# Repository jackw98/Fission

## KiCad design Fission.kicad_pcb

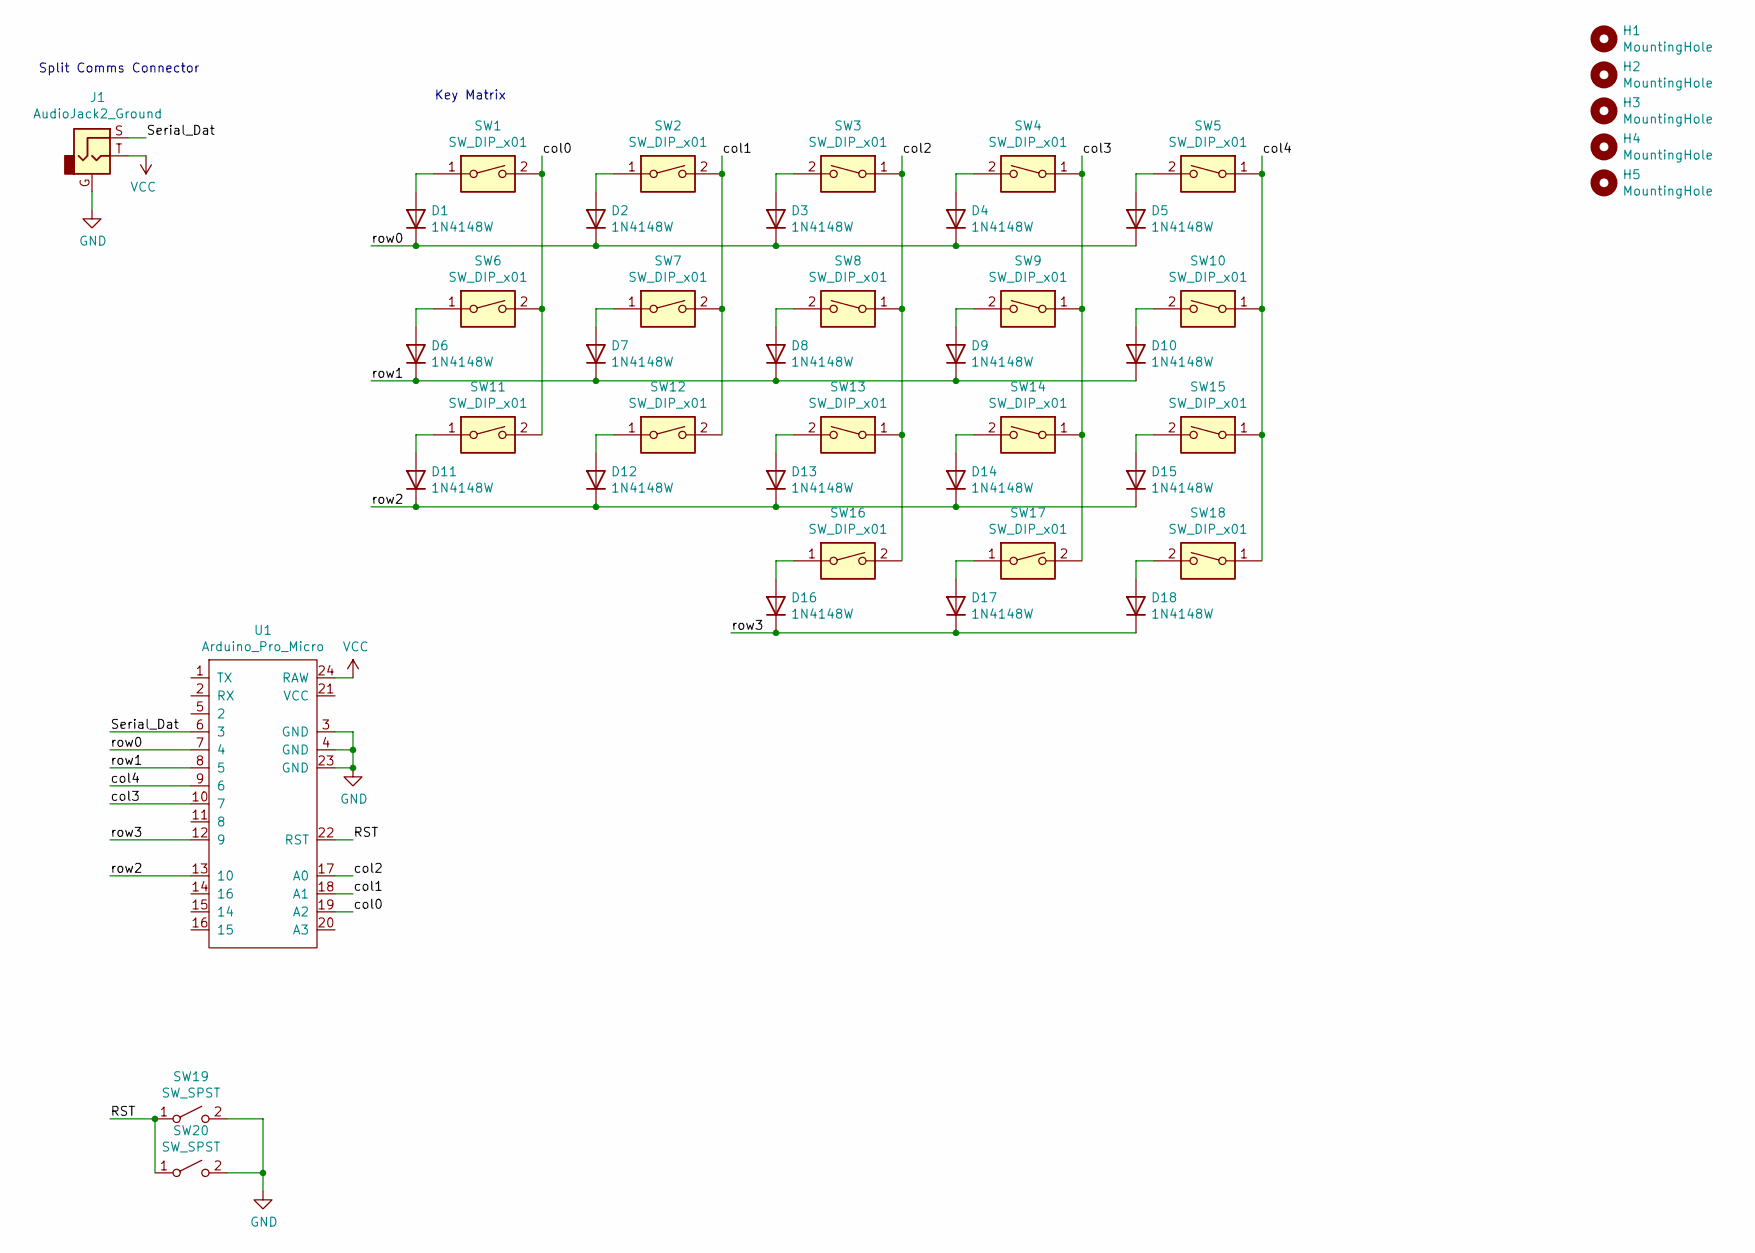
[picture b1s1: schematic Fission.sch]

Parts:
D1, D2, D3, D4, D5, D6, D7, D8, D9, D10, D11, D12, D13, D14, D15, D16, D17, D18: 1N4148W; 1N4148W_Universal_BothSides
H1, H2, H3, H4, H5: MountingHole; MountingHole_2.2mm_M2_Pad_Via
J1: AudioJack2_Ground; Audio_3.5mm_TRS_TH
SW1, SW2, SW3, SW4, SW5, SW6, SW7, SW8, SW9, SW10, SW11, SW12, SW13, SW14, SW15, SW16, SW17, SW18: SW_DIP_x01; SW_Cherry_MX_1.00u_PCB_bothsides
SW19, SW20: SW_SPST; HYP (Hongyuan Precision) 1TS002E-2500-2500-CT
U1: Arduino_Pro_Micro

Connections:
/RST: SW19.1 (A), SW20.1 (A), U1.22 (RST)
/Serial_Dat: J1.S, U1.6 (3)
/col0: SW1.2, SW6.2, SW11.2, U1.19 (A2)
/col1: SW2.2, SW7.2, SW12.2, U1.18 (A1)
/col2: SW3.1, SW8.1, SW13.1, SW16.2, U1.17 (A0)
/col3: SW4.1, SW9.1, SW14.1, SW17.2, U1.10 (7)
/col4: SW5.1, SW10.1, SW15.1, SW18.1, U1.9 (6)
/row0: D1.1 (K), D2.1 (K), D3.1 (K), D4.1 (K), D5.1 (K), U1.7 (4)
/row1: D6.1 (K), D7.1 (K), D8.1 (K), D9.1 (K), D10.1 (K), U1.8 (5)
/row2: D11.1 (K), D12.1 (K), D13.1 (K), D14.1 (K), D15.1 (K), U1.13 (10)
/row3: D16.1 (K), D17.1 (K), D18.1 (K), U1.12 (9)
GND: J1.G, SW19.2 (B), SW20.2 (B), U1.3 (GND), U1.4 (GND), U1.23 (GND)
unnamed: D1.2 (A), SW1.1
unnamed: D2.2 (A), SW2.1
unnamed: D3.2 (A), SW3.2
unnamed: D4.2 (A), SW4.2
unnamed: D5.2 (A), SW5.2
unnamed: D6.2 (A), SW6.1
unnamed: D7.2 (A), SW7.1
unnamed: D8.2 (A), SW8.2
unnamed: D9.2 (A), SW9.2
unnamed: D10.2 (A), SW10.2
unnamed: D11.2 (A), SW11.1
unnamed: D12.2 (A), SW12.1
unnamed: D13.2 (A), SW13.2
unnamed: D14.2 (A), SW14.2
unnamed: D15.2 (A), SW15.2
unnamed: D16.2 (A), SW16.1
unnamed: D17.2 (A), SW17.1
unnamed: D18.2 (A), SW18.2
VCC: J1.T, U1.24 (RAW)

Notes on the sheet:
Split Comms Connector
Key Matrix

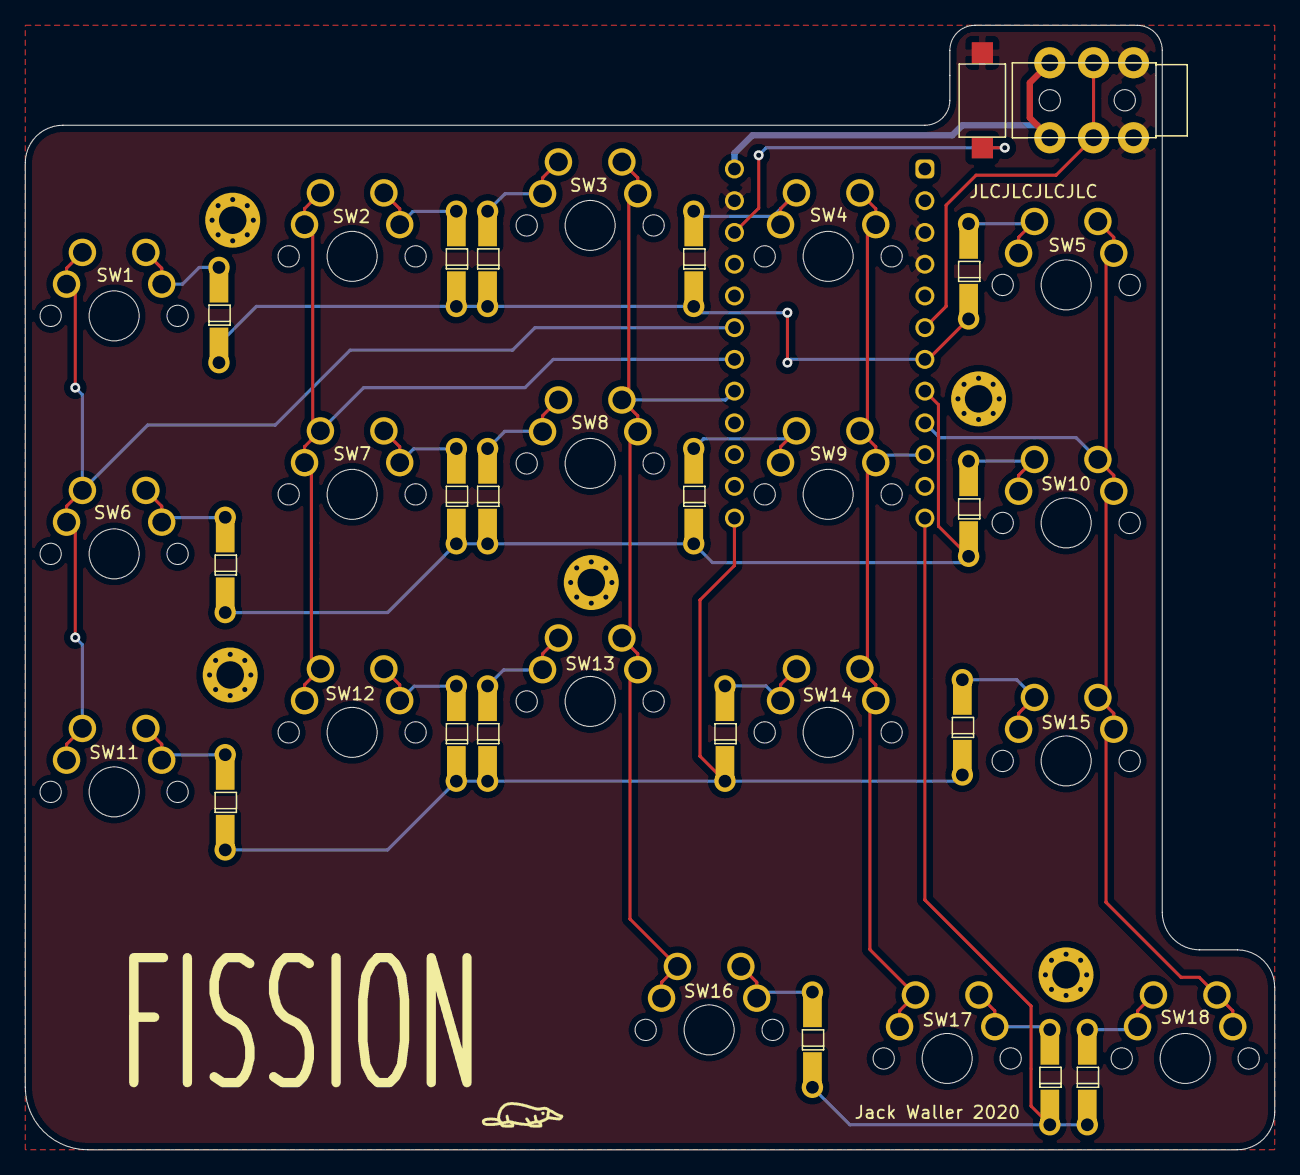
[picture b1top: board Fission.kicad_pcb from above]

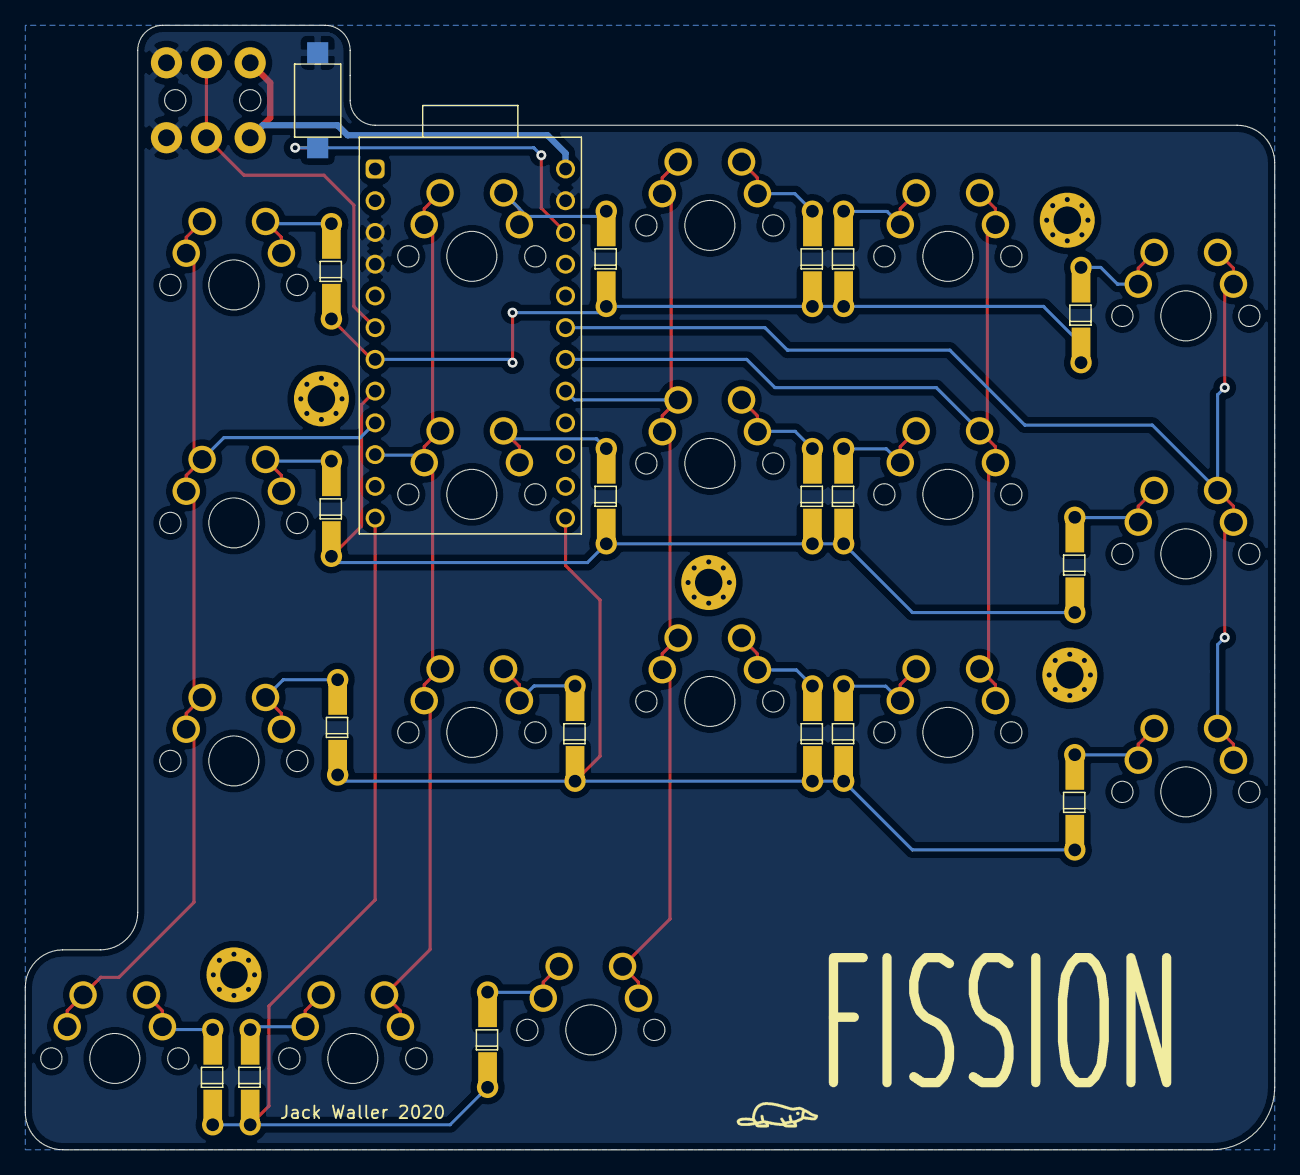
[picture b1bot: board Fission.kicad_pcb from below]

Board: 2 copper layers, 100.0 x 90.0 mm, 45 parts (2 on the bottom side), 31 nets.
